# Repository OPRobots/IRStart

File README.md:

# IRStart

Mando y módulo para el arranque de nuestros robots usando el protocolo RC5.
Basado en: https://p1r.se/startmodule/ por lo que lo hemos hecho compatible
y con un funcionamiento muy similar para que sea apto para competir en la
RoboChallenge de Rumania.

## ⚙️ Hardware

### Módulo
- ATTiny13 SMD SOIC-8
- Receptor IR TSOP4838
- LED azul SMD 0804
- 1 resistencia 220 Ω SMD 0804
- 1 condensador 104 (100 nF) SMD 0402

### Mando
- ESP32 C3 Super Mini
- 3 LEDs IR con MOSFETs (Start/Stop alta intensidad, Ready baja intensidad)
- DIP switch ×4 para configuración de robot (ID)
- NeoPixel RGB ×3 para indicación de estado
- Botones: Start, Stop, Ready, Mode
- Interruptor de encendido
- Módulo de carga de batería LiPo
- Batería LiPo 1S 500 mAh

## 💻 Software

- Programado con PlatformIO (Arduino framework)
- Firmware para módulo (ATtiny13/ATtiny85) y mando (ESP32-C3)
- **Protocolos IR**: RC5, NEC, SIRC
- **Modos**: IRSTART (competición) + IRMENU (control de menú remoto)
- **Frecuencia portadora**: 36 kHz (RC5) / 37 kHz (NEC, SIRC)
- **Debug**: Serial 115200 baud + patrones LED

## 📚 Documentación

- [Hardware](docs/01-hardware.md) — MCUs, pinout, componentes, diseño 3D
- [Arquitectura Software](docs/02-software-architecture.md) — Bucles, ISRs, máquinas de estado
- [Protocolos IR](docs/03-ir-protocols.md) — RC5, NEC, SIRC: codificación y timing
- [Menú](docs/04-menu-system.md) — Modo IRMENU y navegación remota
- [Debug](docs/05-debug-system.md) — Salida serie y patrones LED
- [EEPROM](docs/06-storage.md) — EEPROM del ATtiny
- [Problemas Conocidos](docs/07-known-issues.md) — 10 issues (3 críticos)

## 🔧 Stack Tecnológico

| Componente | Tecnología |
|-----------|-----------|
| **Mando MCU** | ESP32-C3 (RISC-V 160 MHz) |
| **Módulo MCU** | ATtiny13/85 (AVR 8-bit) |
| **Framework** | Arduino |
| **Entorno** | PlatformIO |
| **Lenguaje** | C++11 |
| **Protocolos** | RC5, NEC, SIRC |

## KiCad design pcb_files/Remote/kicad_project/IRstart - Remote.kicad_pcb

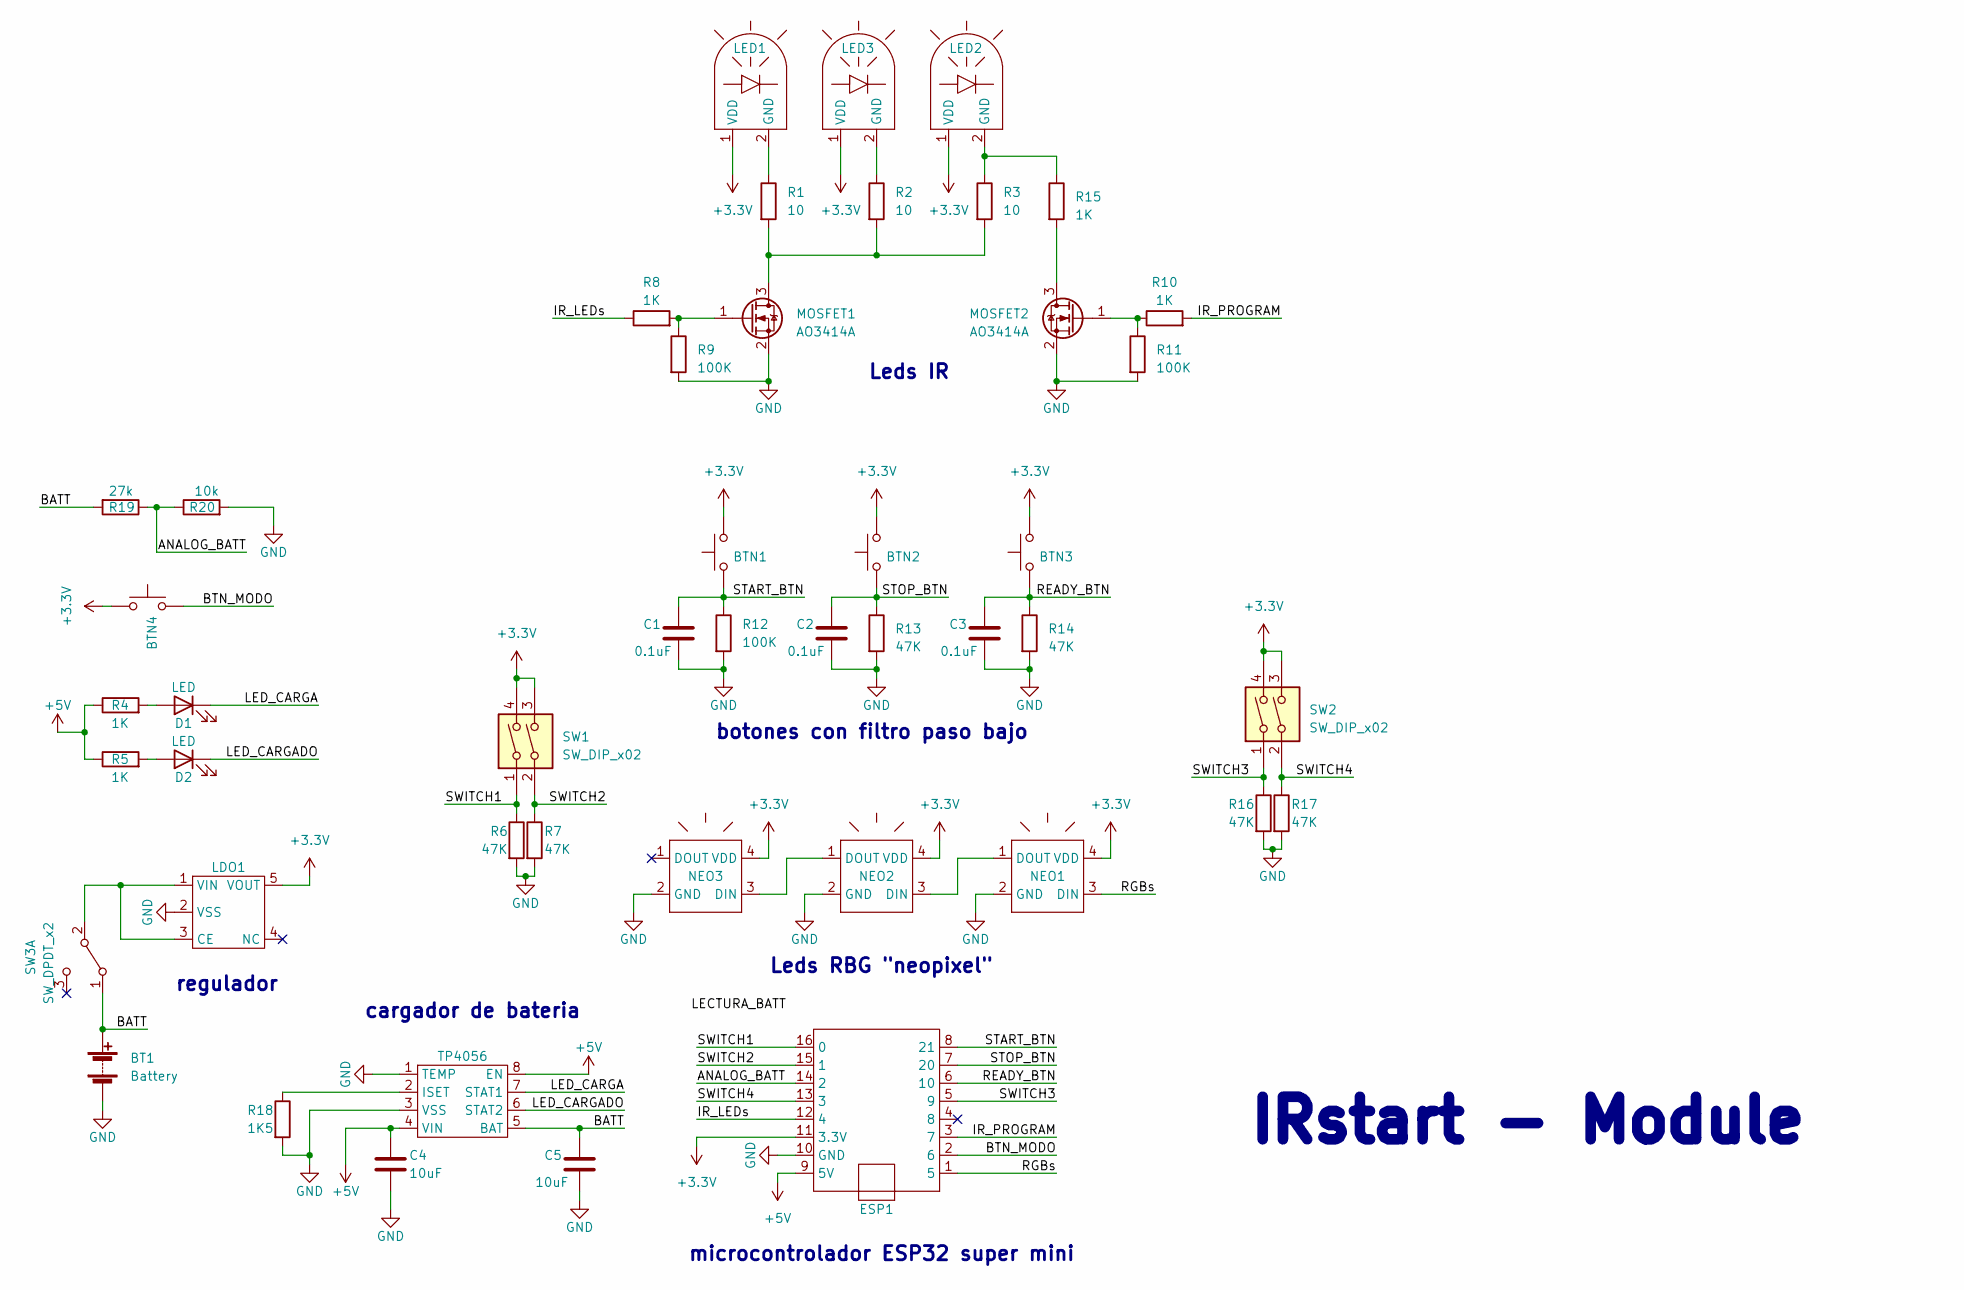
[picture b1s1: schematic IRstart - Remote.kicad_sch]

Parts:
BT1: Battery; Leds_IR_Remote
BTN1, BTN2, BTN3: SW_Push_1P1T_NO_6x6mm_H9.5mm
BTN4: SW_SPST_B3U-1000P
C1, C2, C3: 0.1uF; C_0805_2012Metric_Pad1.18x1.45mm_HandSolder
C4, C5: 10uF; C_0805_2012Metric_Pad1.18x1.45mm_HandSolder
D1, D2: LED; LED_0805_2012Metric_Pad1.15x1.40mm_HandSolder
ESP1: ESP32_supermini
LDO1: SOT-23-5_HandSoldering
LED1, LED2, LED3: Leds_IR_Remote
MOSFET1, MOSFET2: AO3414A; SOT-23
NEO1, NEO2, NEO3: LED_WS2812B_2.0x2.0mm
R1, R2, R3: 10; R_0805_2012Metric_Pad1.20x1.40mm_HandSolder
R4, R5, R8, R10, R15: 1K; R_0805_2012Metric_Pad1.20x1.40mm_HandSolder
R6, R7, R13, R14, R16, R17: 47K; R_0805_2012Metric_Pad1.20x1.40mm_HandSolder
R9, R11, R12: 100K; R_0805_2012Metric_Pad1.20x1.40mm_HandSolder
R18: 1K5; R_0805_2012Metric_Pad1.20x1.40mm_HandSolder
R19: 27k; R_0805_2012Metric_Pad1.20x1.40mm_HandSolder
R20: 10k; R_0805_2012Metric_Pad1.20x1.40mm_HandSolder
SW1, SW2: SW_DIP_x02; SW_DIP_SPSTx02_Slide_6.7x6.64mm_W8.61mm_P2.54mm_LowProfile
SW3: SW_DPDT_x2; SW_SPDT_PCM12
TP4056: SOP-8_3.9x4.9mm_P1.27mm

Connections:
+3.3V: BTN1.2, BTN2.2, BTN3.2, BTN4.2, ESP1.11 (3.3V), LDO1.5 (VOUT), LED1.1 (VDD), LED2.1 (VDD), LED3.1 (VDD), NEO1.4 (VDD), NEO2.4 (VDD), NEO3.4 (VDD), SW1.3, SW1.4, SW2.3, SW2.4
+5V: C4.1, ESP1.9 (5V), R4.1, R5.1, TP4056.4 (VIN), TP4056.8 (EN)
/ANALOG_BATT: ESP1.14 (2), R19.1, R20.1
/BATT: BT1.1 (+), C5.1, R19.2, SW3.1 (A), TP4056.5 (BAT)
/BTN_MODO: BTN4.1, ESP1.2 (6)
/IR_LEDs: ESP1.12 (4), R8.1
/IR_PROGRAM: ESP1.3 (7), R10.2
/LED_CARGA: D1.1 (K), TP4056.7 (STAT1)
/LED_CARGADO: D2.1 (K), TP4056.6 (STAT2)
/READY_BTN: BTN3.1, C3.1, ESP1.6 (10), R14.1
/RGBs: ESP1.1 (5), NEO1.3 (DIN)
/START_BTN: BTN1.1, C1.1, ESP1.8 (21), R12.1
/STOP_BTN: BTN2.1, C2.1, ESP1.7 (20), R13.1
/SWITCH1: ESP1.16 (0), R6.1, SW1.1
/SWITCH2: ESP1.15 (1), R7.1, SW1.2
/SWITCH3: ESP1.5 (9), R16.1, SW2.1
/SWITCH4: ESP1.13 (3), R17.1, SW2.2
GND: BT1.2 (-), C1.2, C2.2, C3.2, C4.2, C5.2, ESP1.10 (GND), LDO1.2 (VSS), MOSFET1.2 (S), MOSFET2.2 (S), NEO1.2 (GND), NEO2.2 (GND), NEO3.2 (GND), R6.2, R7.2, R9.2, R11.2, R12.2, R13.2, R14.2, R16.2, R17.2, R18.2, R20.2, TP4056.1 (TEMP), TP4056.3 (VSS)
unnamed: D1.2 (A), R4.2
unnamed: D2.2 (A), R5.2
unnamed: LDO1.1 (VIN), LDO1.3 (CE), SW3.2 (B)
unnamed: LED1.2 (GND), R1.1
unnamed: LED2.2 (GND), R3.1, R15.1
unnamed: LED3.2 (GND), R2.1
unnamed: MOSFET1.3 (D), R1.2, R2.2, R3.2
unnamed: MOSFET1.1 (G), R8.2, R9.1
unnamed: MOSFET2.3 (D), R15.2
unnamed: MOSFET2.1 (G), R10.1, R11.1
unnamed: NEO1.1 (DOUT), NEO2.3 (DIN)
unnamed: NEO2.1 (DOUT), NEO3.3 (DIN)
unnamed: R18.1, TP4056.2 (ISET)

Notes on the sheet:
IRstart - Module
cargador de bateria
Leds IR
Leds RBG "neopixel"
regulador
microcontrolador ESP32 super mini
botones con filtro paso bajo

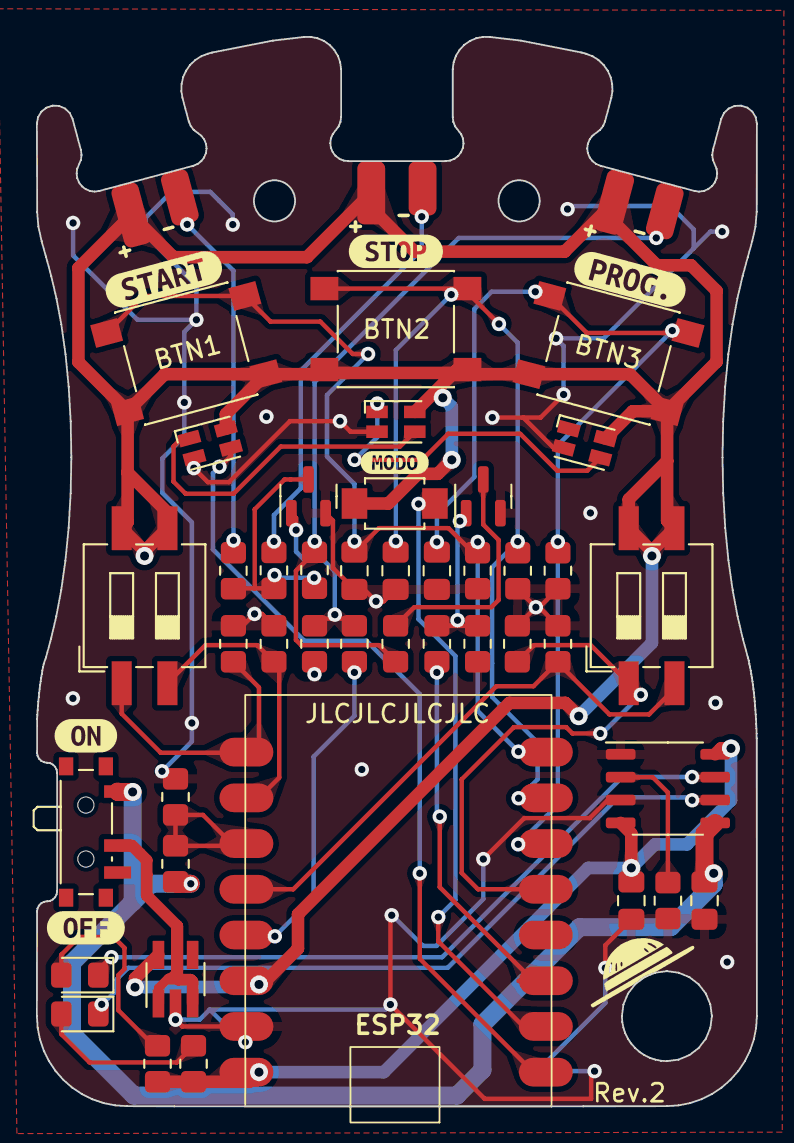
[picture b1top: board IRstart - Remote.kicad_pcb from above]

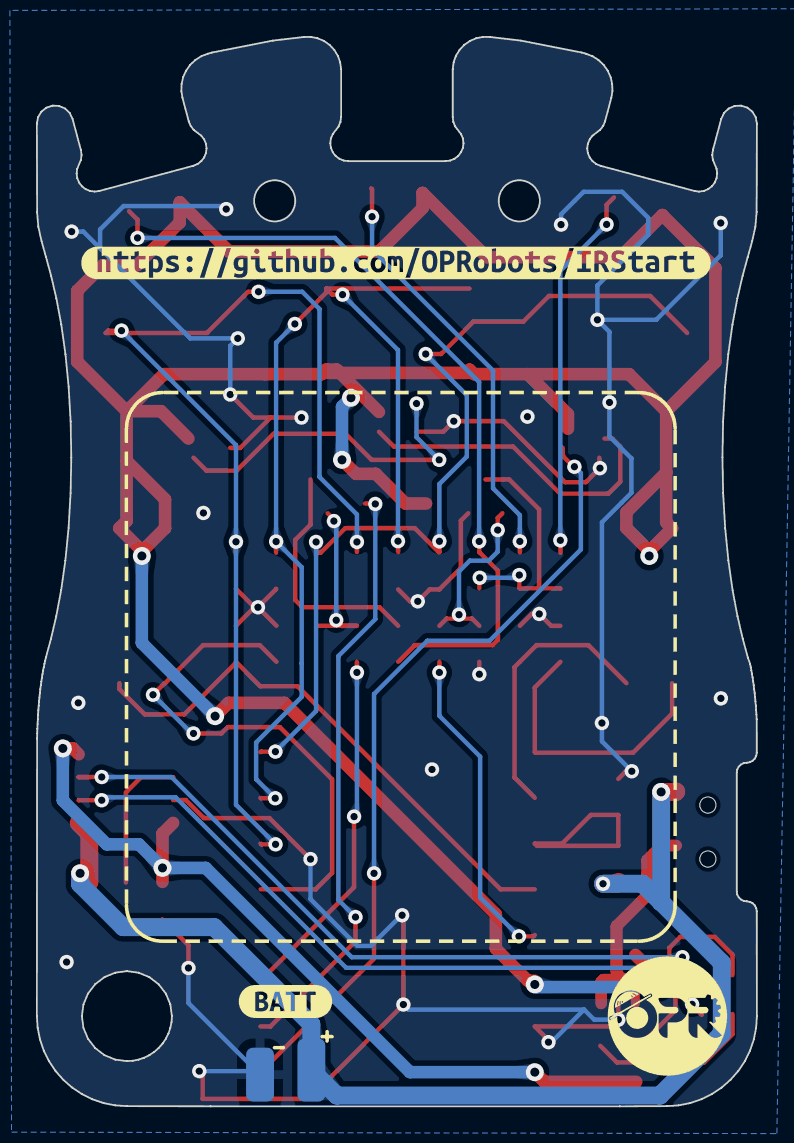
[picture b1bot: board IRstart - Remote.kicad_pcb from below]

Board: 2 copper layers, 40.0 x 59.4 mm, 54 parts (3 on the bottom side), 31 nets.

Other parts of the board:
kibuzzard-664F31E4: G***; kibuzzard-664F31E4
kibuzzard-673F80D1: G***; kibuzzard-673F80D1
kibuzzard-673F8949: G***; kibuzzard-673F8949
kibuzzard-673F8963: G***; kibuzzard-673F8963
kibuzzard-6637BAEA: G***; kibuzzard-6637BAEA
kibuzzard-6637BBE8: G***; kibuzzard-6637BBE8
kibuzzard-6637BC1A: G***; kibuzzard-6637BC1A
kibuzzard-6637DAEE: G***; kibuzzard-6637DAEE

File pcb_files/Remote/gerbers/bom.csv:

Designator,Footprint,Quantity,Value,LCSC Part #
BT1,Leds_IR_Remote,1,Battery,
"BTN1, BTN2, BTN3",SW_Push_1P1T_NO_6x6mm_H9.5mm,3,~,
"C1, C2, C3",0805,3,0.1uF,
"C4, C5",0805,2,10uF,
"D1, D2",0805,2,LED,
ESP1,ESP32_supermini,1,~,
LDO1,SOT-23-5_HandSoldering,1,~,
"LED1, LED2, LED3",Leds_IR_Remote,3,~,
"MOSFET1, MOSFET2",SOT-23,2,AO3414A,
"NEO1, NEO2, NEO3",LED_WS2812B_2.0x2.0mm,3,~,
"R1, R2, R3",0805,3,150,
"R10, R15, R4, R5, R8",0805,5,1K,
"R11, R9",0805,2,100K,
"R12, R13, R14, R16, R17, R6, R7",0805,7,47K,
R18,0805,1,1K5,
R19,0805,1,0,
"SW1, SW2",SW_DIP_SPSTx02_Slide_6.7x6.64mm_W8.61mm_P2.54mm_LowProfile,2,SW_DIP_x02,
SW3,SW_SPDT_PCM12,1,SW_DPDT_x2,
TP4056,SOP-8_3.9x4.9mm_P1.27mm,1,~,

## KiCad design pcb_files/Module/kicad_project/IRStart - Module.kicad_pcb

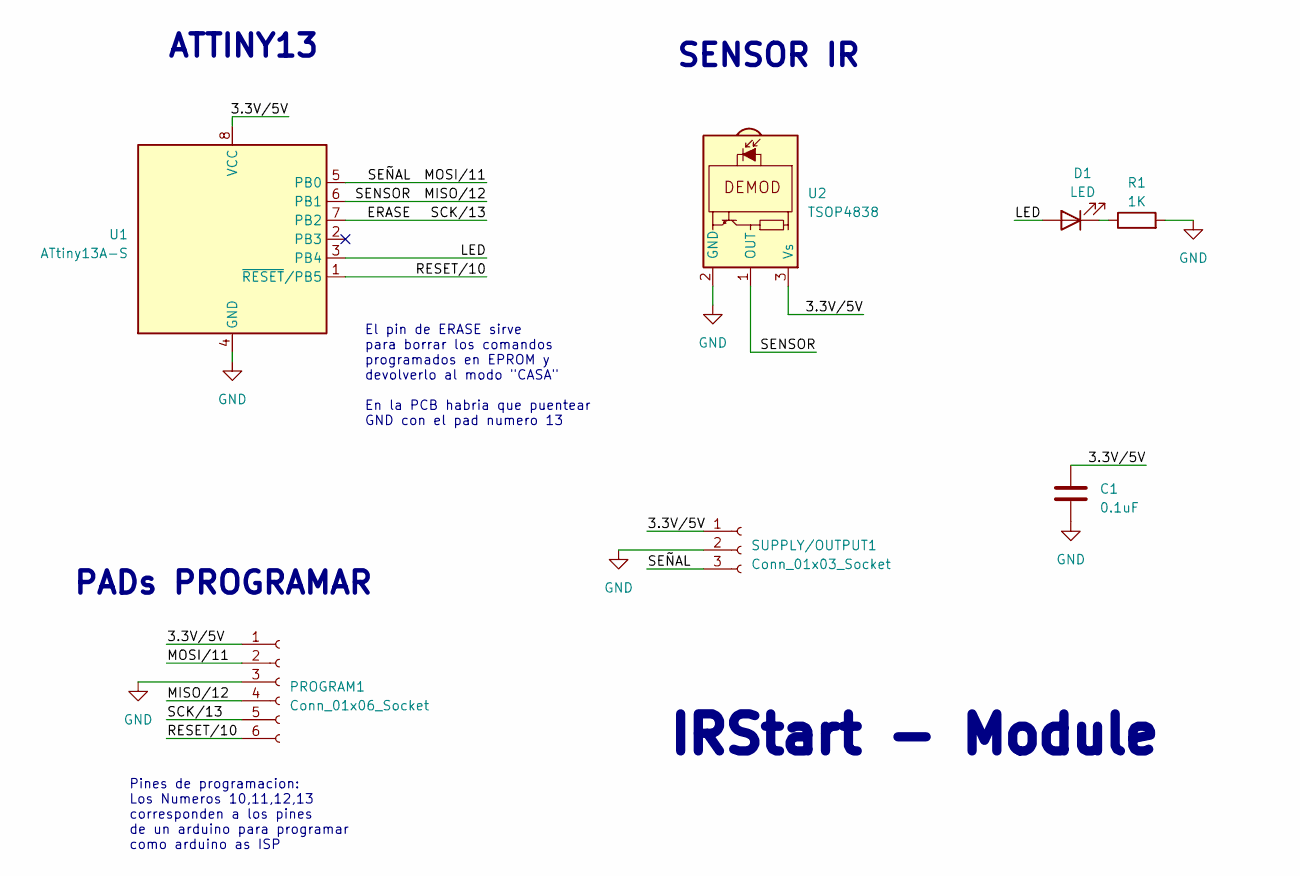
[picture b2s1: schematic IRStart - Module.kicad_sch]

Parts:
C1: 0.1uF; C_0402_1005Metric_Pad0.74x0.62mm_HandSolder
D1: LED; LED_0805_2012Metric
PROGRAM1: Conn_01x06_Socket; Program_pads
R1: 1K; R_0805_2012Metric
SUPPLY/OUTPUT1: Conn_01x03_Socket; PinSocket_1x03_P2.54mm_Vertical
U1: ATtiny13A-S; SOP8
U2: TSOP4838; Vishay_MOLD-3Pin

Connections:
/3.3V/5V: C1.1, PROGRAM1.1, SUPPLY/OUTPUT1.1, U1.8 (VCC), U2.3 (Vs)
/ERASE: PROGRAM1.5, U1.7 (PB2)
/LED: D1.2 (A), U1.3 (PB4)
/MISO/12: PROGRAM1.4, U1.6 (PB1), U2.1 (OUT)
/MOSI/11: PROGRAM1.2, SUPPLY/OUTPUT1.3, U1.5 (PB0)
/RESET/10: PROGRAM1.6, U1.1 (~RESET/PB5)
GND: C1.2, PROGRAM1.3, R1.2, SUPPLY/OUTPUT1.2, U1.4 (GND), U2.2 (GND)
unnamed: D1.1 (K), R1.1

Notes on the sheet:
SENSOR IR
PADs PROGRAMAR
El pin de ERASE sirve para borrar los comandos programados en EPROM y devolverlo al modo "CASA" En la PCB habria que puentear GND con el pad numero 13
ATTINY13
IRStart - Module
Pines de programacion: Los Numeros 10,11,12,13 corresponden a los pines de un arduino para programar como arduino as ISP

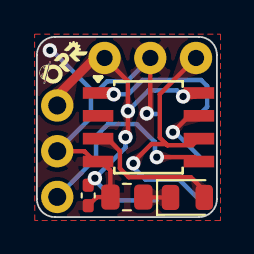
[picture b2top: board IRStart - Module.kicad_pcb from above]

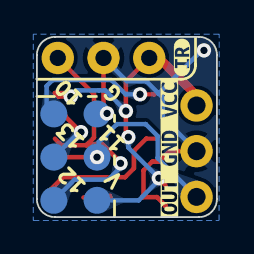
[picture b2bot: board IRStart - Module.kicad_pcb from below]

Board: 2 copper layers, 10.0 x 10.0 mm, 9 parts (3 on the bottom side), 8 nets.

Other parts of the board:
kibuzzard-664B9D8E: G***; kibuzzard-664B9D8E
kibuzzard-664B97EA: G***; kibuzzard-664B97EA

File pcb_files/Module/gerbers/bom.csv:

Designator,Footprint,Quantity,Value,LCSC Part #
C1,0402,1,C,
D1,0805,1,LED,
PROGRAM1,Program_pads,1,Conn_01x06_Socket,
R1,0805,1,1K,
SUPPLY/OUTPUT1,PinSocket_1x03_P2.54mm_Vertical,1,Conn_01x03_Socket,
U1,SOP8,1,ATtiny13A-S,
U2,Vishay_MOLD-3Pin,1,TSOP45xx,

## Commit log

2023-08-18 Añade los ficheros del proyecto
2023-08-18 Actualiza readme añadiendo datos de Hardware e Imágenes
2024-04-21 Añade carpetas para IRstart - Remote y empieza el proyecto de kicad
2024-04-21 Avanza con el diseño del mando. Acaba esquema y ordena componentes PCB
2024-05-05 Avanza con el diseño de la PCB
2024-05-23 Añade nuevos proyectos KiCad de Module y Remote y normaliza repo
2024-05-23 Elimina fichero temporal
2024-05-24 Añade gerbers de remote y adecenta el esquematico
2024-05-24 Añade modelos 3D y pone bonito los "renders"
2024-05-24 Añade modelo 3D de TSOP4838 para el Module
2024-05-24 Actualiza custom libraries del Remote
2024-06-12 Añade código inicial del Remote
2024-06-12 Realiza los cambios necesarios para la PCB de IRStart
2024-06-19 Añade funcionamiento de RGBs
2024-06-19 Corrige leds RGB con huella incorrecta
2024-10-01 Añade imagines del diseño y de las PCBs montadas
2024-10-01 Añade imagen de mando y modulo montados
2024-10-01 Añade código del módulo para ATTiny13 y ATTiny85
2024-10-01 Actualiza recursos step y elimina imágenes antiguas
2024-10-06 Añade envío de comandos para modificar el menú de los robots
2024-11-20 Añade diseños 3d y stls
2024-11-21 Crea la Rev.2 del mando añadiendo boton de modo y lectura de bateria
2025-01-28 Añade soporte para modo IRMENU
2026-06-25 Añalde ajustes antiguos para soporte a modo menú
2026-06-25 Añade STL de la carcasa del mando
2026-06-25 Añade documentación MkDocs
2026-06-25 Actualiza rutas de imágenes en documentación
2026-06-25 Actualiza enlaces de referencia de software
